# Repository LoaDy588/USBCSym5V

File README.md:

# USBC Symetric 5V Power module

Continued from https://github.com/JarekParal/USBCPowerModule.

## Device
### TPS65131
Split-Rail Converter with Dual, Positive and Negative Outputs (750mA typ)    	
http://www.ti.com/product/tps65131   
http://www.ti.com/lit/gpn/tps65131   

### LM2990
1-A, Negative Low Dropout Regulator  
http://www.ti.com/product/lm2990    
http://www.ti.com/lit/gpn/lm2990   

### LM2940C
1A Low Dropout Regulator   
http://www.ti.com/product/lm2940c   
http://www.ti.com/lit/ds/symlink/lm2940c.pdf    

## Problems
 * Still not tested at full power capability, according to datasheet calculations it is overloaded by factor of 2 at full 1A output

 * TPS65131 is seemingly the most powerful split rail converter, higher currents would require separate boost and inverting converters.

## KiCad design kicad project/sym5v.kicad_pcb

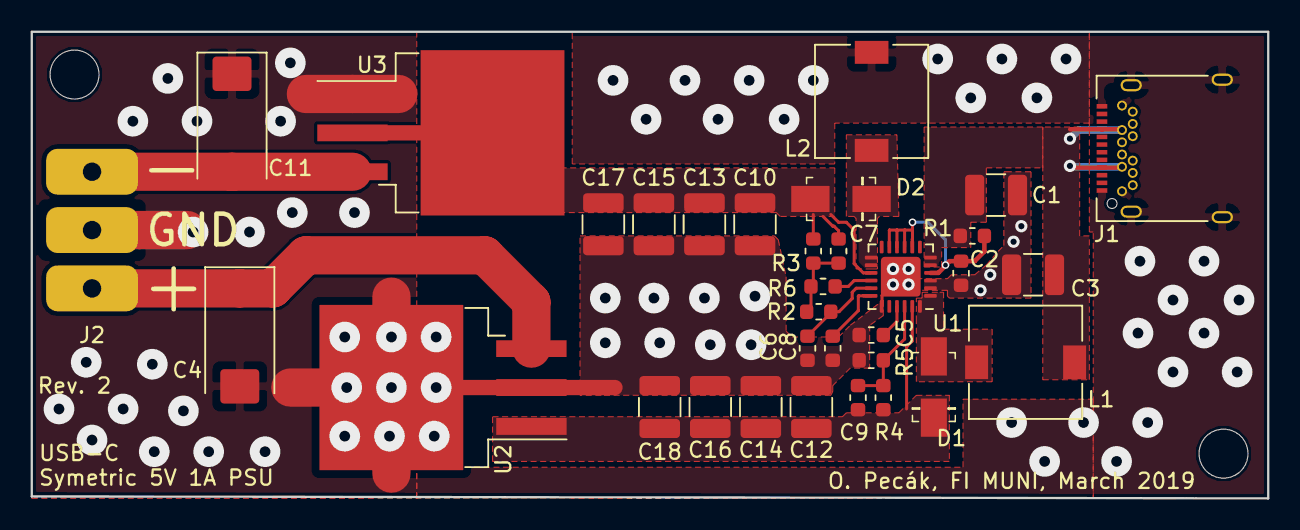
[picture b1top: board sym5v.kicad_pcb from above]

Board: 2 copper layers, 80.8 x 30.5 mm, 33 parts (0 on the bottom side), 15 nets.

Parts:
C1, C3, C10, C12, C13, C14, C15, C16, C17, C18: 4.7uF; C_1210_3225Metric
C2: 100nF; C_0603_1608Metric
C4, C11: 47uF; CP_EIA-7343-31_Kemet-D_Pad2.25x2.55mm_HandSolder
C5: 10nF; C_0603_1608Metric
C6: 220nF; C_0603_1608Metric
C7: 10pF or 12pF; C_0603_1608Metric
C8: 4.7nF; C_0603_1608Metric
C9: 12pF; C_0603_1608Metric
D1, D2: D_Schottky; DO-214AC
J1: USB_C_Receptacle; USB_C_Receptacle_Amphenol_12401548E4-2A
J2: Conn_01x03; SolderWirePad_1x03_P3.81mm_Drill1.2mm
L1: 2.2uH; L_7.3x7.3_H3.5
L2: 3.3uH; L_7.3x7.3_H3.5
R1: 100R; R_0603_1608Metric
R2, R5: 130K; R_0603_1608Metric
R3: 665K; R_0603_1608Metric
R4: 536K; R_0603_1608Metric
R6: 100K; R_0603_1608Metric
U1: TPS6513x; QFN-24-1EP_4x4mm_P0.5mm_EP2.6x2.6mm
U2: LM2940; TO-263-3_TabPin4
U3: LM2990SX-5.0; TO-263-3_TabPin2

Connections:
+5V: C4.1, J2.1, U2.3
-5V: C11.2, J2.3, U3.3
GND: C1.2, C2.2, C3.2, C4.2, C5.2, C6.2, C8.2, C10.2, C11.1, C12.2, C13.2, C14.2, C15.2, C16.2, C17.2, C18.2, J1.A1, J1.A12, J1.B1, J1.B12, J1.S1, J2.2, L2.2, R5.2, U1.2, U1.3, U1.19, U2.2, U2.4, U3.1
unnamed: C2.1, R1.1, U1.4, U1.8, U1.9, U1.10, U1.11
unnamed: C5.1, U1.21
unnamed: C6.1, R2.1, U1.17
unnamed: C7.1, R2.2, R3.1, R6.1
unnamed: C8.1, U1.18
unnamed: C9.2, R4.2, R5.1, U1.22
unnamed: D1.2, L1.2, U1.1, U1.24
unnamed: D2.1, L2.1, U1.13, U1.14
unnamed: R6.2, U1.16
VIN: C1.1, C3.1, J1.A4, J1.A9, J1.B4, J1.B9, L1.1, R1.2, U1.5, U1.6
VNEG: C7.2, C10.1, C13.1, C15.1, C17.1, D2.2, R3.2, U1.15, U3.2
VPOS: C9.1, C12.1, C14.1, C16.1, C18.1, D1.1, R4.1, U1.23, U2.1

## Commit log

2018-08-23 init
2018-08-26 Rev1
2019-03-13 Rev 2 schematic - broken symbols!
2019-03-13 rev2 final
2019-03-14 add mounting holes
2019-03-28 Add case
